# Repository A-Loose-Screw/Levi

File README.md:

# Levi
Personal Robot Project

### Levi Robot:

### Robot Core Lib

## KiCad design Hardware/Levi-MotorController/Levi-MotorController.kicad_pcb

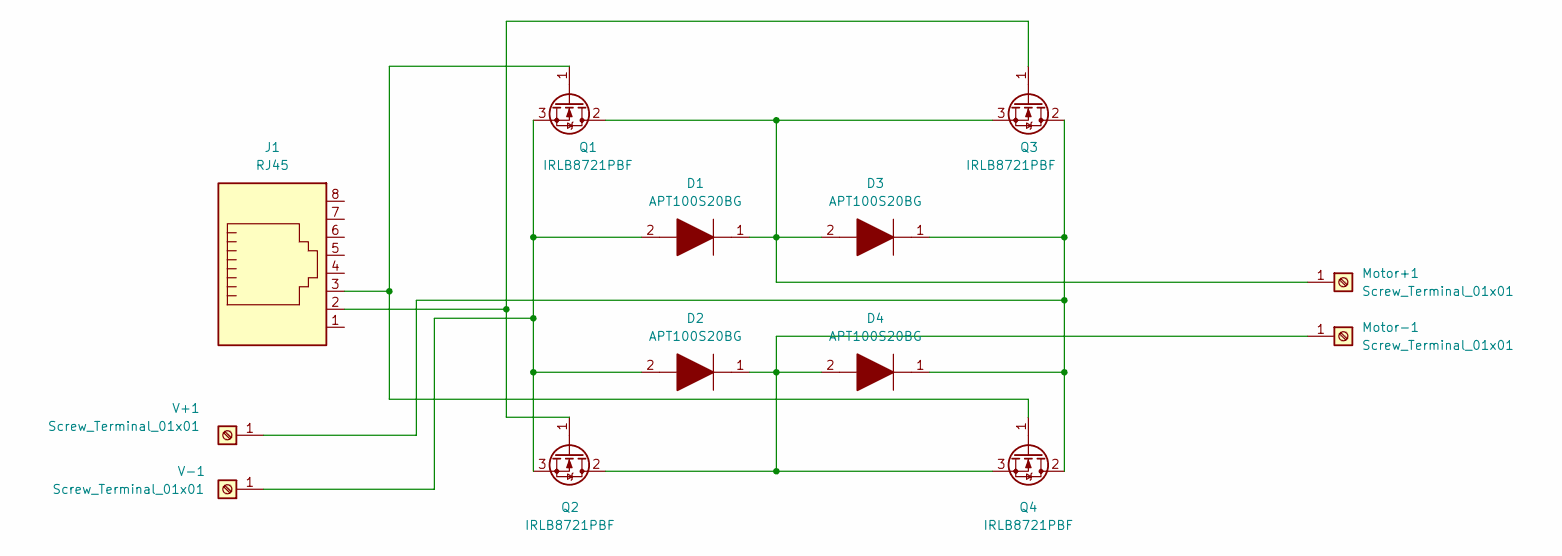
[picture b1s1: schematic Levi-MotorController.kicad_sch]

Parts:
D1, D2, D3, D4: APT100S20BG; TO1087P531X1588X2596-2P; Mouser Part Number 494-APT100S20BG
J1: RJ45; RJ45_Amphenol_RJHSE538X
Motor+1: Screw_Terminal_01x01; Wuerth_REDCUBE-THR_WP-THRSH_74651195_THR
Motor-1: Screw_Terminal_01x01; Wuerth_REDCUBE-THR_WP-THRSH_74651195_THR
Q1, Q2, Q3, Q4: IRLB8721PBF; TO-220-3_Horizontal_TabUp
V+1: Screw_Terminal_01x01; Wuerth_REDCUBE-THR_WP-THRSH_74651195_THR
V-1: Screw_Terminal_01x01; Wuerth_REDCUBE-THR_WP-THRSH_74651195_THR

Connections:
unnamed: D1.1, D3.2, Motor+1.1, Q1.2 (D), Q3.3 (S)
unnamed: D2.1, D4.2, Motor-1.1, Q2.2 (D), Q4.3 (S)
unnamed: J1.2, Q2.1 (G), Q3.1 (G)
unnamed: J1.3, Q1.1 (G), Q4.1 (G)
unnamed: D1.2, D2.2, Q1.3 (S), Q2.3 (S), V-1.1
unnamed: D3.1, D4.1, Q3.2 (D), Q4.2 (D), V+1.1

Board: 2 copper layers, 13 parts (0 on the bottom side), 6 nets, no tracks yet.

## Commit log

2022-06-08 Added Core Application Build Script
2022-06-08 Checkpoint
2022-06-08 Added RobotCore submodule
2022-06-09 Switched remote for submodule
2022-06-10 Fixed up buildable code
2022-06-10 Set up CI with Azure Pipelines
    [skip ci]
2022-06-10 Update azure-pipelines.yml for Azure Pipelines
2022-06-10 Added the Status Badge
2022-06-10 Added Azure for windows & mac jobs:
2022-06-10 Added status badge
2022-06-12 Added robot core base
2022-07-14 Added dev code
2022-08-03 Adding schematic
2022-08-04 adding footprints
2022-08-04 loaded proper model
2022-12-16 Windows patch
2022-12-16 Fixed up submodule
2022-12-16 Added prototype motor controller
2022-12-16 Testing cmd args
2022-12-16 Updated RBC
2022-12-17 Fixed up robot core gtest (removed)
2022-12-20 Fixed up thread sleep issues on windows
2022-12-25 Combus addition to RBC
2023-01-29 removed hardware from code
